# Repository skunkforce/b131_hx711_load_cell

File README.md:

# edgy_board number b131
This design is part of the [edgy board project](https://github.com/skunkforce/edgy_boards). It provides the functionality of chip XXXX via interfaces YYYY. 

# getting started
This repository uses submodules. After cloning use the command 

```$ git submodule update --init --recursive```

to pull the submodules before opening the project with kicad. 

# Tests
Tests can be found in [TESTS.md](TESTS.md)

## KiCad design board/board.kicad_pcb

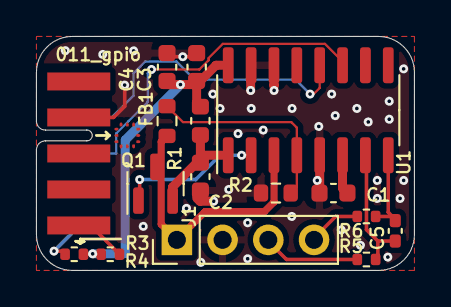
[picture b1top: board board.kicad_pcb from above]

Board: 2 copper layers, 21.0 x 13.0 mm, 17 parts (1 on the bottom side), 15 nets.

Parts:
C1, C2, C3, C4: 0.1uF; C_0603_1608Metric
C5: 0.1uF; C_0402_1005Metric_Pad0.74x0.62mm_HandSolder
FB1: >=1k; L_0603_1608Metric
J1: Conn_01x04_Male; PinHeader_1x04_P2.54mm_Vertical
J2: 002_SPI; debug_edge_2x05_device
LOGO1: Logo_Open_Hardware_Small; OSHW-Symbol_6.7x6mm_SilkScreen
Q1: BC807; SOT-23
R1, R2: 10k; R_0603_1608Metric
R3, R4: 0/DNP; R_0402_1005Metric
R5, R6: 100; R_0402_1005Metric
U1: hx711; SOP-16_3.9x9.9mm_P1.27mm

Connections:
/hx711_hall/AVDD: J1.1, Q1.3 (C), R1.1, U1.3 (AVDD)
/hx711_hall/BASE: Q1.1 (B), U1.2 (BASE)
/hx711_hall/DOUT: J2.3 (MISO), U1.12 (DOUT)
/hx711_hall/DVDD: C3.1, C4.1, FB1.2, R3.2, R4.1, U1.16 (DVDD)
/hx711_hall/INNA: J1.3, R5.1
/hx711_hall/INPA: J1.4, R6.1
/hx711_hall/PD_SCK: J2.4 (SCLK), U1.11 (PD_SCK)
/hx711_hall/VBG: C1.1, U1.6 (VBG)
/hx711_hall/VFB: R1.2, R2.1, U1.4 (VFB)
/hx711_hall/VIN: J2.9 (3.3V), R4.2
/hx711_hall/VIN_5: J2.10 (5V), R3.1
/hx711_hall/VSUP: C2.1, FB1.1, Q1.2 (E), U1.1 (VSUP)
GND: C1.2, C2.2, C3.2, C4.2, J1.2, J2.1 (GND), R2.2, U1.5 (AGND), U1.14 (XI), U1.15 (RATE)
unnamed: C5.1, R5.2, U1.7 (INNA)
unnamed: C5.2, R6.2, U1.8 (INPA)
